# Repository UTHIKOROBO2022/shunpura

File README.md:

## はじめに  

2021年12月に開催された「第17回全日本学生飛行ロボットコンテスト」に東京大学の有志学生が集まって参加したチーム「瞬着とプライマーよこせ！」のメンバーが、出場機体に搭載した半自動操縦用の制御回路とソースコードを全て公開します！  

<br>

## ファイルリスト  

|ファイル名|説明|
|:--|:--|
|Neve.pdf|回路図PDF|
|Neve.sch|EAGLE回路図ファイル|
|Neve.brd|EAGLEボード図ファイル|
|control_Neve.ino|Arduinoソースファイル|
|CAD|機体の設計データ|

回路図ファイルとボード図ファイルは、Fusion360で作成したものをEAGLE形式で出力しています。

<br>

## 制御について  

本チームは自動操縦部門ではなく一般部門に出場しましたが、飛行を安定させ操縦しやすくするため、独自にマイコンや6軸ジャイロセンサを搭載して半自動操縦を実現しています。すなわち、手元の送信機の左スティックで姿勢角の目標値を与え、機体に搭載したマイコンでそれに追従するよう制御を行っています。また、S.BUS信号のCh.5に半自動操縦のON/OFF、Ch.6に投下機構の動作をアサインしています。

<br>

## 主な使用部品  

|部品名|説明|  
|:--|:--|  
|Arduino Nano Every|制御マイコン|  
|GY-521|MPU-6050搭載6軸ジャイロセンサ|  
|Futaba R3001SB|受信機|  

マイコンは必ずArduino Nano Everyを使用します。Arduino Nanoでは動作しません。  
基板上に実装する電子部品については、回路図を参照して下さい。

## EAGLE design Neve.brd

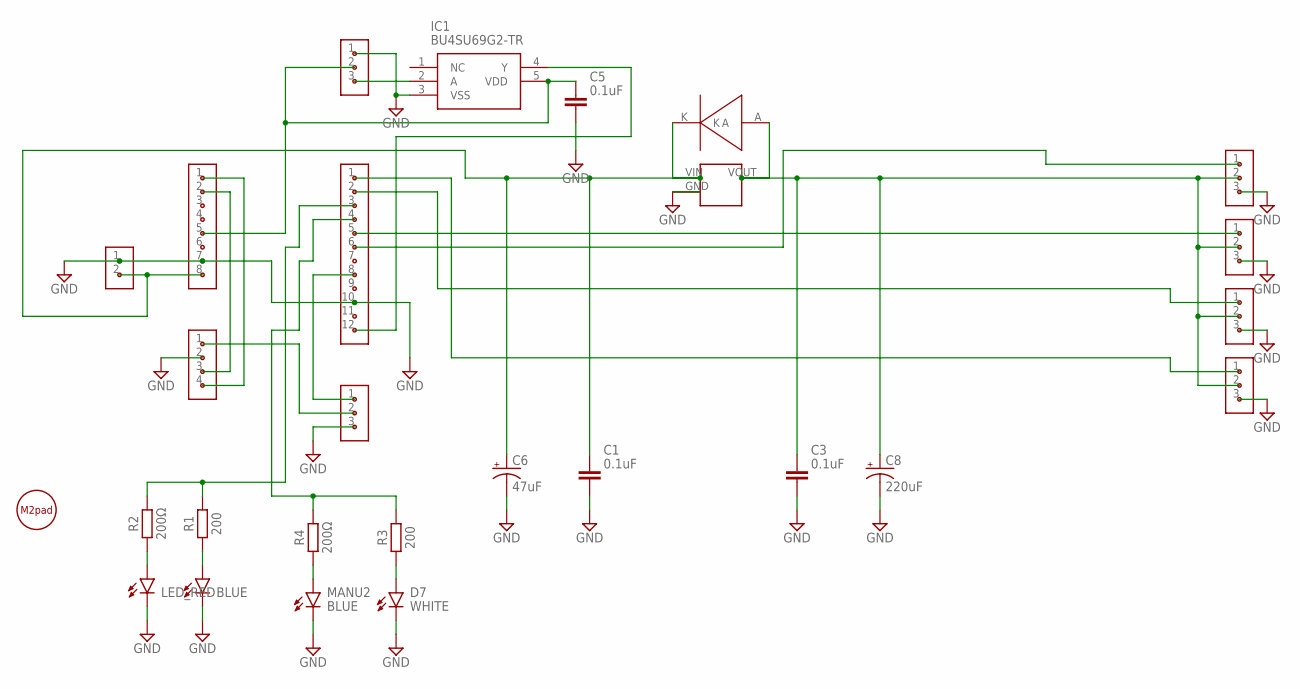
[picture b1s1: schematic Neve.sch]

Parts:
AUTO2: LED_RED; LEDC1608X65N_RND-R
C1, C3, C5: 0.1uF; CAPC2012X110
C6: 47uF; 153CLV-0605
C8: 220uF; 153CLV-0605
D7: WHITE; LEDC1608X65N_RND-R
D8: BLUE; LEDC1608X65N_RND-R
DIODE1: CRG01
IC1: BU4SU69G2-TR; SOT95P280X125-5N
JP1, JP2, JP3, JP4, JP5, JP8: PIN_1X3
JP6: PIN_1X4
JP7: PIN_1X2
JP9: PIN_1X12
JP10: PIN_1X8
MANU2: BLUE; LEDC1608X65N_RND-R
R1, R3: 200; RESC2012X65
R2, R4: 200Ω; RESC2012X65
RG1: NJM7805SDL1
U$1: M2PAD

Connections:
ARDUINO_5V: C5.1, IC1.5 (VDD), JP8.2, JP10.5
D3_PWM: JP5.1, JP9.8
D5_PWM: JP1.1, JP9.6
D6_PWM: JP2.1, JP9.5
D7_LED_MA: JP9.4, R3.2, R4.2
D8_LED_AU: JP9.3, R1.2, R2.2
D9_PWM: JP3.1, JP9.2
D10_PWM: JP4.1, JP9.1
ESC_5V: JP5.2, JP6.1
GND: AUTO2.C, C1.2, C3.2, C5.2, C6.-, C8.-, D7.C, D8.C, IC1.3 (VSS), JP1.3, JP2.3, JP3.3, JP4.3, JP5.3, JP6.2, JP7.1, JP8.1, JP9.10, JP10.7, MANU2.C, RG1.GND
LIPO_2S: C1.1, C6.+, DIODE1.K, JP7.2, JP10.8, RG1.VIN
unnamed: JP6.3, JP10.2
unnamed: JP6.4, JP10.1
unnamed: MANU2.A, R4.1
unnamed: D8.A, R1.1
unnamed: D7.A, R3.1
unnamed: AUTO2.A, R2.1
SBUS: IC1.2 (A), JP8.3
SERVO_5V: C3.1, C8.+, DIODE1.A, JP1.2, JP2.2, JP3.2, JP4.2, RG1.VOUT
UART: IC1.4 (Y), JP9.12

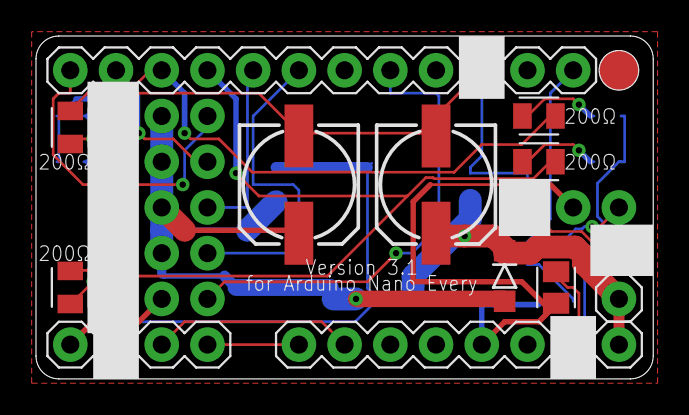
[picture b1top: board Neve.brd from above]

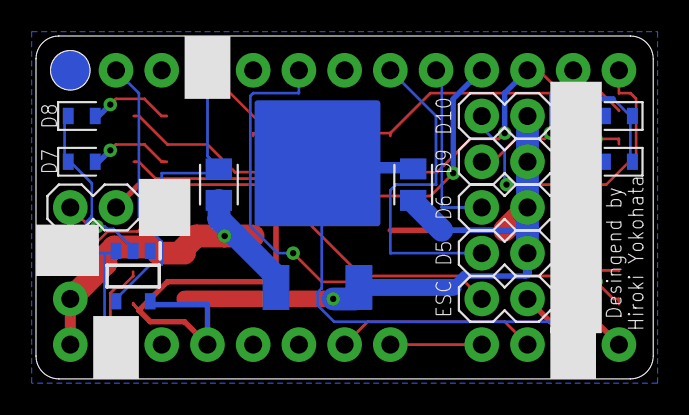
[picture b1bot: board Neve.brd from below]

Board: 2 copper layers, 34.3 x 19.0 mm, 27 parts (14 on the bottom side), 20 nets.

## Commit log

2022-04-12 CAD追加したよん
